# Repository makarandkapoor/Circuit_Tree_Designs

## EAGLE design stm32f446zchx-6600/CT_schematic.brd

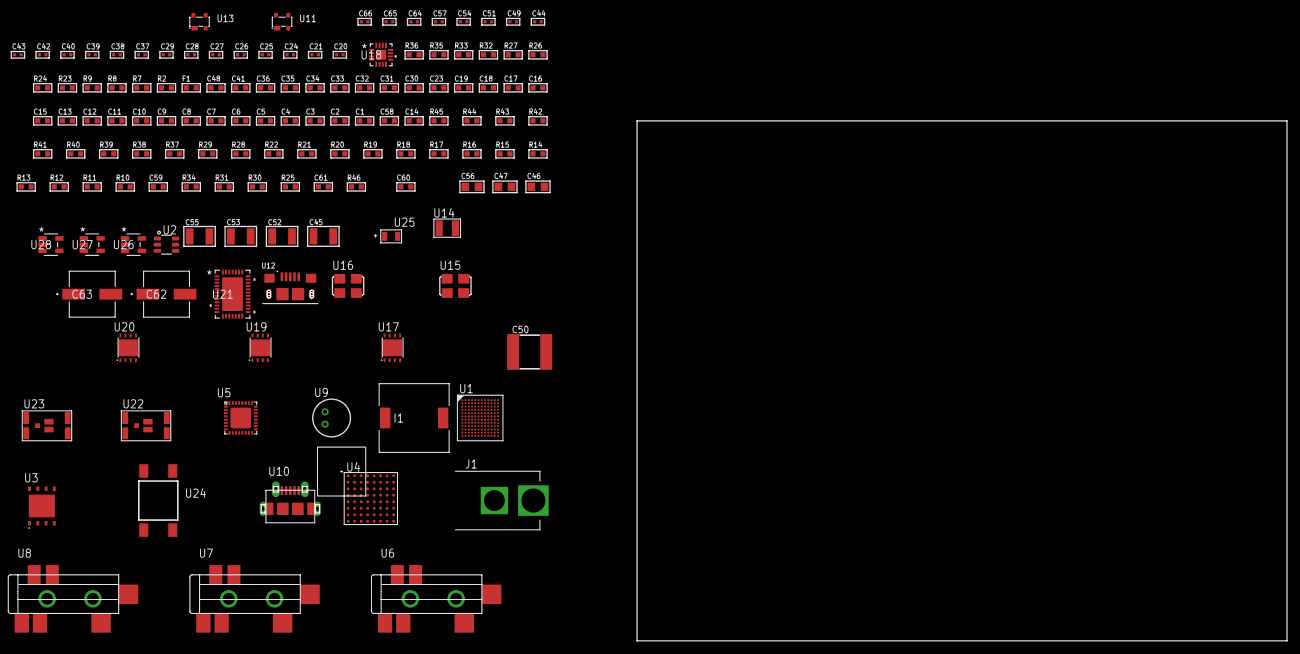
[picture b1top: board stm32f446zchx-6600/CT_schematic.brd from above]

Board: 2 copper layers, 137 parts (0 on the bottom side), 131 nets, no tracks yet.

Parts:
C1, C16, C23, C30, C31, C32, C33, C34, C35, C36, C41, C48: 1e-06; C0603
C2, C3, C4, C5, C6, C7, C8, C9, C10, C11, C12, C13, C17, C18, C19: 1e-07; C0603
C14: 4.7e-06; C0603
C15: 1e-08; C0603
C20, C21: 1e-11; C0402
C24, C26, C28, C37, C38, C39, C40, C49, C57: 1e-07; C0402
C25, C27, C29, C42, C43, C44, C51, C54, C64, C65, C66: 1e-08; C0402
C45, C52, C53, C55: 1e-05; C1210
C46, C47, C56: 1e-05; C0805
C50: 6.8e-05; 2220
C58: 2.2e-06; C0603
C59: 2.45e-08; R0603
C60: 2.8258362168397e-09; R0603
C61: 7.105e-09; R0603
C62, C63: 0.0001; EXV-9H
F1: 240.0; L0603
I1: 5.2e-06; DR1040
J1: PJ-037B; PJ-037B_PACKAGE
R2, R27, R33, R36: 1000.0; R0603
R7, R8, R9: 4700.0; R0603
R10: 47000.0; R0603
R11, R12, R13, R14, R15, R16, R17, R18, R19, R20, R21, R22, R37, R39, R40, R43, R44, R45: 10000.0; R0603
R23, R24: 1270.0; R0603
R25, R31, R34: 100000.0; R0603
R26, R35: 200.0; R0603
R28: 20000.0; R0603
R29: 91000.0; R0603
R30: 300000.0; R0603
R32: 3900.0; R0603
R38: 75000.0; R0603
R41, R42: 95300.0; R0603
R46: 120272.72727273; R0603
U1: STM32F446ZCH6; UFBGA144
U2: MAX4995AAUT+T; SOT-23-6
U3: MX25R6435FZAIH0; WSON-8-PAD
U4: PC28F512P33BFD
U5: SGTL5000XNAA3; QFN-32
U6, U7, U8: SJ-43515TS-SMT-TR
U9: WM-64PCT; WM-64PC
U10: 47590-0001; MICRO_USB_AB
U11, U13: prtr5v0u2ax; SOT143B
U12: 10118193-0001LF; FCI_10118193-0001LF
U14: ABS07-32.768KHZ-7-T
U15: ASFL-24.57MHZ-NCS; ASFL1
U16: ASFL1-25MHZ-NCS; ASFL1
U17, U19, U20: LP3878SDX-ADJ/NOPB; WSON-8
U18: LTC3601EUD#PBF; QFN-16_EP
U21: LTC2928CUHF#PBF; QFN-38_UHF
U22, U23: IRF8306MTRPbF; IRF8306MTRPBF
U24: 4-1437565-2; SW_4-1437565-2
U25: Q65110A2395; LGM67K-G1J2-24-Z
U26, U27, U28: nc7sz125m5x; NC7SZ125M5X

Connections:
CLK_CRYSTAL_U1_B1: C20.1, U1.B1, U14.1
CLK_CRYSTAL_U1_C1: C21.1, U1.C1, U14.2
CLK_U1_D1: U1.D1, U16.3
CLK_U5_21: U5.21, U15.3
GND: C1.2, C2.2, C3.2, C4.2, C5.2, C6.2, C7.2, C8.2, C9.2, C10.2, C11.2, C12.2, C13.2, C14.2, C15.2, C16.2, C17.2, C18.2, C19.2, C20.2, C21.2, C23.2, C24.2, C25.2, C26.2, C27.2, C28.2, C29.2, C37.2, C38.2, C39.2, C40.2, C41.2, C42.2, C43.2, C44.2, C45.2, C46.2, C47.2, C48.2, C50.1, C50.2, C51.2, C52.2, C53.2, C54.2, C55.2, C56.2, C57.2, C58.2, C59.2, C60.2, C61.2, C62.2, C63.2, C64.2, C65.2, C66.2, J1.2, R2.2, R10.2, R11.2, R15.2, R24.2, R27.2, R28.2, R30.2, R33.2, R36.2, R38.2, R41.2, R42.2, R43.2, R44.2, R45.2, U1.D2, U1.E6, U1.E7, U1.G4, U1.G8, U1.G10, U1.H6, U1.J1, U1.K1, U2.2, U3.4, U3.PAD, U4.B2, U4.H2, U4.H4, U4.H6, U5.1, U5.3, U5.7, U5.EXP, U7.1, U8.1, U9.2, U10.5, U10.6, U10.7, U10.8, U10.9, U11.1, U12.5, U12.6, U12.7, U12.8, U12.9, U13.1, U15.2, U16.2, U17.3, U17.PAD, U18.1, U18.9, U18.17, U19.3, U19.PAD, U20.3, U20.PAD, U21.8, U21.9, U21.10, U21.12, U21.13, U21.24, U21.25, U21.30, U21.32, U21.39, U25.C, U26.1, U26.3, U27.1, U27.3, U28.1, U28.3
NET_U1_D5: R11.1, U1.D5
NET_U1_E5: R12.1, U1.E5
NET_U1_F1: R9.1, U1.F1, U28.4
NET_U1_G9: C19.1, U1.G9
NET_U1_H5: R13.1, U1.H5
NET_U1_M1: C15.1, C16.1, F1.1, U1.L1, U1.M1
NET_U1_M11: U24.3, U24.4
NET_U2_3: R10.1, U2.3
NET_U3_7: R7.1, U1.F3, U3.7, U26.4
NET_U4_A4: C28.1, C29.1, U4.A4
NET_U4_C6: R21.1, U4.C6
NET_U4_D4: R8.1, U4.D4, U27.4
NET_U5_10: C40.1, U5.10
NET_U5_29: R23.1, U5.29
NET_U5_31: R24.1, U5.31
NET_U6_1: U5.4, U6.1
NET_U6_2: U5.2, U6.2
NET_U6_5: U5.6, U6.5
NET_U7_2: C31.1, U7.2
NET_U7_5: C30.1, U7.5
NET_U8_2: C33.1, C34.1, U8.2
NET_U8_5: C32.1, U8.5
NET_U8_13: C33.2, C34.2
NET_U9_1: C35.1, C36.1, C41.1, U5.16, U9.1
NET_U9_15: C35.2, C36.2
NET_U17_1: C44.1, U17.1
NET_U17_6: R26.2, R27.1, U17.6
NET_U17_8: R25.1, U17.8
NET_U18_3: C49.2, I1.1, U18.3, U18.4
NET_U18_6: C49.1, U18.6
NET_U18_7: C48.1, U18.7, U18.12
NET_U18_10: R30.1, U18.10
NET_U18_11: R28.1, R29.1, U18.11
NET_U18_ATNET_3: I1.2, R29.2
NET_U19_1: C51.1, U19.1
NET_U19_6: R32.2, R33.1, U19.6
NET_U19_8: R31.1, U19.8
NET_U20_1: C54.1, U20.1
NET_U20_6: R35.2, R36.1, U20.6
NET_U20_8: R34.1, U20.8
NET_U21_3: R44.1, U21.3
NET_U21_6: R41.1, U21.6
NET_U21_7: R42.1, U21.7
NET_U21_16: R43.1, R46.1, U21.16
NET_U21_18: R40.1, U21.18
NET_U21_19: R39.1, U21.19, U21.20
NET_U21_21: R37.1, R38.1, U21.21, U26.2, U27.2, U28.2
NET_U21_22: C57.1, R37.2, R39.2, R40.2, U21.11, U21.22
NET_U21_26: C60.1, U21.26
NET_U21_27: C59.1, U21.27
NET_U21_28: C61.1, U21.28
NET_U21_38: R45.1, U21.38
NET_U22_3: U21.2, U22.3
NET_U23_3: U21.37, U23.3
NET_U24_1: R2.1, U24.1, U24.2
PROC_FMC_A0: U1.C3, U4.A1
PROC_FMC_A1: U1.C4, U4.B1
PROC_FMC_A2: U1.D4, U4.C1
PROC_FMC_A3: U1.E2, U4.D1
PROC_FMC_A4: U1.E3, U4.D2
PROC_FMC_A5: U1.E4, U4.A2
PROC_FMC_A6: U1.L5, U4.C2
PROC_FMC_A7: U1.K5, U4.A3
PROC_FMC_A8: U1.M6, U4.B3
PROC_FMC_A9: U1.L6, U4.C3
PROC_FMC_A10: U1.K6, U4.D3
PROC_FMC_A11: U1.J6, U4.C4
PROC_FMC_A12: U1.J12, U4.A5
PROC_FMC_A13: U1.J11, U4.B5
PROC_FMC_A14: U1.J10, U4.C5
PROC_FMC_A15: U1.H12, U4.D7
PROC_FMC_A16: U1.H9, U4.D8
PROC_FMC_A17: U1.L10, U4.A7
PROC_FMC_A18: U1.K10, U4.B7
PROC_FMC_A19: U1.A2, U4.C7
PROC_FMC_A20: U1.B2, U4.C8
PROC_FMC_A21: U1.B3, U4.A8
PROC_FMC_A22: U1.B4, U4.G1
PROC_FMC_A23: U1.A3, U4.H8
PROC_FMC_A24: U1.D7, U4.B6
PROC_FMC_CLK: U1.D9, U4.E6
PROC_FMC_D0: U1.K11, U4.F2
PROC_FMC_D1: U1.K12, U4.E2
PROC_FMC_D2: U1.E10, U4.G3
PROC_FMC_D3: U1.D10, U4.E4
PROC_FMC_D4: U1.M7, U4.E5
PROC_FMC_D5: U1.L7, U4.G5
PROC_FMC_D6: U1.K7, U4.G6
PROC_FMC_D7: U1.J7, U4.H7
PROC_FMC_D8: U1.H8, U4.E1
PROC_FMC_D9: U1.J8, U4.E3
PROC_FMC_D10: U1.K8, U4.F3
PROC_FMC_D11: U1.L8, U4.F4
PROC_FMC_D12: U1.M8, U4.F5
PROC_FMC_D13: U1.L9, U4.H5
PROC_FMC_D14: U1.K9, U4.G7
PROC_FMC_D15: U1.J9, U4.E7
PROC_FMC_NE2: R19.1, U1.E8, U4.B4
PROC_FMC_NL: R18.1, U1.D6, U4.F6
PROC_FMC_NOE: R20.1, U1.C9, U4.F8
PROC_FMC_NWAIT: U1.A8, U4.F7
PROC_FMC_NWE: R22.1, U1.B9, U4.G8
PROC_GPIO_TO_U1_USB_FAULT: R14.1, U1.A4, U2.6
PROC_GPIO_TO_U1_VBUS_EN: R15.1, U1.A1, U2.4
PROC_I2S1_CK: U1.A7, U5.24
PROC_I2S1_SD: U1.B6, U5.26
PROC_I2S1_WS: U1.A10, U5.23
PROC_QUADSPI_BK1_IO0: U1.E11, U3.5
PROC_QUADSPI_BK1_IO1: U1.B11, U3.2
PROC_QUADSPI_BK1_IO2: R17.1, U1.F2, U3.3
PROC_QUADSPI_BK1_NCS: R16.1, U1.C6, U3.1
PROC_QUADSPI_CLK: U1.J5, U3.6
PROC_USB_OTG_FS_DM: U1.C12, U10.2, U11.3
PROC_USB_OTG_FS_DP: U1.B12, U10.3, U11.2
PROC_USB_OTG_FS_ID: U1.D11, U10.4
PROC_USB_OTG_FS_VBUS: U1.D12, U2.1, U10.1, U11.4
PROC_USB_OTG_HS_DM: U12.2, U13.3
PROC_USB_OTG_HS_DP: U12.3, U13.2
PROC_USB_OTG_HS_VBUS: U12.1, U13.4
VCC_14V6: C58.1, C62.1, C63.1, J1.1, R46.2, U21.23, U22.1, U22.2, U22.6, U22.7, U23.1, U23.2, U23.6, U23.7
VCC_S1_14V6: C45.1, C47.1, C52.1, R25.2, R31.2, U17.4, U18.15, U18.16, U19.4, U22.4, U22.5
VCC_S2_14V6: C55.1, R34.2, U20.4, U23.4, U23.5
VCC_TIER1_1V2: C18.1, C37.1, C46.1, R26.1, U1.H7, U5.30, U17.5
VCC_TIER1_3V3: C1.1, C2.1, C3.1, C4.1, C5.1, C6.1, C7.1, C8.1, C9.1, C10.1, C11.1, C12.1, C13.1, C14.1, C17.1, C23.1, C24.1, C25.1, C26.1, C27.1, C38.1, C39.1, C42.1, C43.1, C50.2, C64.1, C65.1, C66.1, F1.2, I1.2, R7.2, R8.2, R9.2, R12.2, R13.2, R14.2, R16.2, R17.2, R18.2, R19.2, R20.2, R21.2, R22.2, R23.2, R29.2, U1.C2, U1.C11, U1.D3, U1.F4, U1.F5, U1.F6, U1.F7, U1.F8, U1.F9, U1.F10, U1.G5, U1.G6, U1.G7, U3.8, U4.A6, U4.D5, U4.D6, U4.G4, U4.H3, U5.5, U5.20, U15.4, U16.4, U18.8, U26.5, U27.5, U28.5
VCC_TIER1_5V0: C53.1, R32.1, U2.5, U19.5
VCC_TIER2_1V2: C56.1, R35.1, U20.5

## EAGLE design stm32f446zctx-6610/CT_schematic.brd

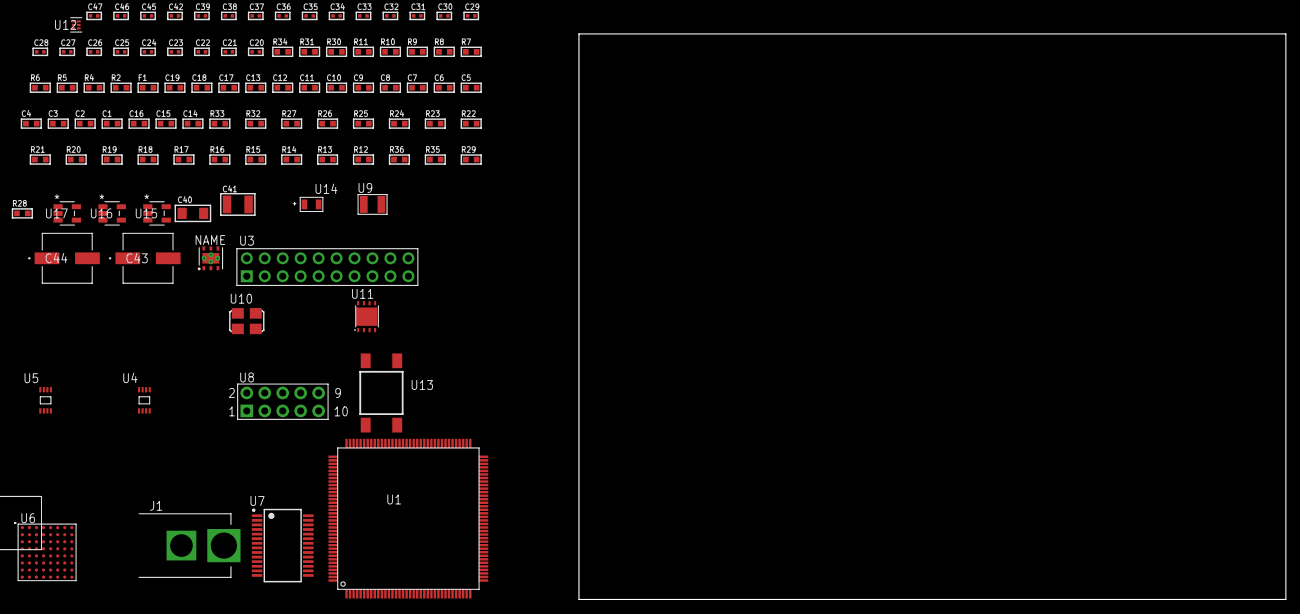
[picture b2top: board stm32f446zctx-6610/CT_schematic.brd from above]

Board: 2 copper layers, 100.0 x 80.0 mm, 100 parts (0 on the bottom side), 97 nets, no tracks yet.

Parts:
C1, C18: 1e-06; C0603
C2, C3, C4, C5, C6, C7, C8, C9, C10, C11, C12, C13, C19: 1e-07; C0603
C14: 4.7e-06; C0603
C15, C16: 2.2e-06; C0603
C17: 1e-08; C0603
C20, C21: 1e-11; C0402
C22, C25, C26, C28, C30, C32, C38, C39, C45, C46, C47: 1e-08; C0402
C23, C24, C27, C29, C31, C33, C34, C35, C36, C37, C42: 1e-07; C0402
C40: 1e-05; C1206
C41: 1e-05; C1210
C43, C44: 0.0001; EXV-9H
F1: 240.0; L0603
J1: PJ-037B; PJ-037B_PACKAGE
R2, R31: 1000.0; R0603
R4, R5: 4700.0; R0603
R6, R7, R8, R9, R10, R11: 2200.0; R0603
R12, R13, R14, R15, R16, R17, R18, R19, R20, R21, R22, R23, R24, R25, R26, R27, R32, R33: 10000.0; R0603
R28, R29: 100000.0; R0603
R30: 2231.0; R0603
R34: 9100.0; R0603
R35: 680000.0; R0603
R36: 120000.0; R0603
U1: STM32F446ZCT6; LQFP144
U2: HDC1080DMBR; WSON-6
U3: TST-110-05-T-D-RA
U4: 24AA01T-I/MNY; TDFN-8/6MM
U5: 24AA64T-I/MNY; TDFN-8/6MM
U6: PC28F512P33BFD
U7: ST3241EBPR; SSOP-28
U8: HTSS-105-01-G-D
U9: ABS07-32.768KHZ-7-T
U10: ASFL1-25MHZ-NCS; ASFL1
U11: LP3878SDX-ADJ/NOPB; WSON-8
U12: TPS3895ADRYR; SON-6
U13: 4-1437565-2; SW_4-1437565-2
U14: Q65110A2395; LGM67K-G1J2-24-Z
U15, U16, U17: nc7sz125m5x; NC7SZ125M5X

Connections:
CLK_CRYSTAL_U1_8: C20.1, U1.8, U9.1
CLK_CRYSTAL_U1_9: C21.1, U1.9, U9.2
CLK_U1_23: U1.23, U10.3
GND: C1.2, C2.2, C3.2, C4.2, C5.2, C6.2, C7.2, C8.2, C9.2, C10.2, C11.2, C12.2, C13.2, C14.2, C15.2, C16.2, C17.2, C18.2, C19.2, C20.2, C21.2, C22.2, C23.2, C24.2, C25.2, C26.2, C27.2, C28.2, C29.2, C30.2, C31.2, C32.2, C33.2, C36.2, C37.2, C38.2, C39.2, C40.2, C41.2, C42.2, C43.2, C44.2, C45.2, C46.2, C47.2, J1.2, R2.2, R12.2, R19.2, R20.2, R21.2, R31.2, R34.2, R36.2, U1.16, U1.31, U1.38, U1.51, U1.61, U1.83, U1.94, U1.107, U1.120, U1.130, U2.2, U2.PAD, U3.4, U3.6, U3.8, U3.10, U3.12, U3.14, U3.16, U3.18, U3.20, U4.4, U5.4, U5.7, U6.B2, U6.H2, U6.H4, U6.H6, U7.23, U7.25, U8.9, U10.2, U11.3, U11.PAD, U12.2, U14.C, U15.2, U15.3, U16.1, U16.3, U17.1, U17.3
NET_U1_25: R5.1, U1.25, U17.4
NET_U1_33: C17.1, C18.1, F1.1, U1.32, U1.33
NET_U1_69: R8.1, U1.69, U5.6
NET_U1_70: R9.1, U1.70, U5.5
NET_U1_71: C15.1, U1.71
NET_U1_99: R11.1, U1.99, U4.5
NET_U1_100: R10.1, U1.100, U4.6
NET_U1_106: C16.1, U1.106
NET_U1_136: R6.1, U1.136, U2.6
NET_U1_138: R12.1, U1.138
NET_U1_140: R7.1, U1.140, U2.1
NET_U1_142: U13.3, U13.4
NET_U1_143: R13.1, U1.143
NET_U3_19: R19.1, U3.19
NET_U5_1: R20.1, U5.1
NET_U5_2: R21.1, U5.2
NET_U5_3: R22.1, U5.3
NET_U6_A4: C31.1, C32.1, U6.A4
NET_U6_C6: R26.1, U6.C6
NET_U6_D4: R4.1, U6.D4, U16.4
NET_U7_1: C35.1, U7.1
NET_U7_2: C35.2, U7.2
NET_U7_3: C37.1, U7.3
NET_U7_22: R28.1, U7.22
NET_U7_24: C34.2, U7.24
NET_U7_27: C36.1, U7.27
NET_U7_28: C34.1, U7.28
NET_U8_3: U7.4, U8.3
NET_U8_4: U7.5, U8.4
NET_U8_5: U7.9, U8.5
NET_U8_6: U7.10, U8.6
NET_U11_1: C39.1, U11.1
NET_U11_6: R30.2, R31.1, U11.6
NET_U11_8: R29.1, U11.8
NET_U12_1: R33.1, R34.1, U12.1
NET_U12_3: R35.2, R36.1, U12.3
NET_U12_4: R32.1, U12.4, U15.4, U16.2, U17.2
NET_U13_1: R2.1, U13.1, U13.2
PROC_FMC_A0: U1.10, U6.A1
PROC_FMC_A1: U1.11, U6.B1
PROC_FMC_A2: U1.12, U6.C1
PROC_FMC_A3: U1.13, U6.D1
PROC_FMC_A4: U1.14, U6.D2
PROC_FMC_A5: U1.15, U6.A2
PROC_FMC_A6: U1.50, U6.C2
PROC_FMC_A7: U1.53, U6.A3
PROC_FMC_A8: U1.54, U6.B3
PROC_FMC_A9: U1.55, U6.C3
PROC_FMC_A10: U1.56, U6.D3
PROC_FMC_A11: U1.57, U6.C4
PROC_FMC_A12: U1.87, U6.A5
PROC_FMC_A13: U1.88, U6.B5
PROC_FMC_A14: U1.89, U6.C5
PROC_FMC_A15: U1.90, U6.D7
PROC_FMC_A16: U1.80, U6.D8
PROC_FMC_A17: U1.81, U6.A7
PROC_FMC_A18: U1.82, U6.B7
PROC_FMC_A19: U1.2, U6.C7
PROC_FMC_A20: U1.3, U6.C8
PROC_FMC_A21: U1.4, U6.A8
PROC_FMC_A22: U1.5, U6.G1
PROC_FMC_A23: U1.1, U6.H8
PROC_FMC_A24: U1.128, U6.B6
PROC_FMC_CLK: U1.117, U6.E6
PROC_FMC_D0: U1.85, U6.F2
PROC_FMC_D1: U1.86, U6.E2
PROC_FMC_D2: U1.114, U6.G3
PROC_FMC_D3: U1.115, U6.E4
PROC_FMC_D4: U1.58, U6.E5
PROC_FMC_D5: U1.59, U6.G5
PROC_FMC_D6: U1.60, U6.G6
PROC_FMC_D7: U1.63, U6.H7
PROC_FMC_D8: U1.64, U6.E1
PROC_FMC_D9: U1.65, U6.E3
PROC_FMC_D10: U1.66, U6.F3
PROC_FMC_D11: U1.67, U6.F4
PROC_FMC_D12: U1.68, U6.F5
PROC_FMC_D13: U1.77, U6.H5
PROC_FMC_D14: U1.78, U6.G7
PROC_FMC_D15: U1.79, U6.E7
PROC_FMC_NE2: R24.1, U1.124, U6.B4
PROC_FMC_NL: R23.1, U1.137, U6.F6
PROC_FMC_NOE: R25.1, U1.118, U6.F8
PROC_FMC_NWAIT: U1.122, U6.F7
PROC_FMC_NWE: R27.1, U1.119, U6.G8
PROC_SYS_JTCK_SWCLK: R17.1, U1.109, U3.9
PROC_SYS_JTDI: R15.1, U1.110, U3.5
PROC_SYS_JTDO_SWO: U1.133, U3.13
PROC_SYS_JTMS_SWDIO: R16.1, U1.105, U3.7
PROC_SYS_JTRST: R14.1, U1.134, U3.3
RST_OUT_U3_SRESET_B: R18.1, U3.15, U15.1
VCC_S1_7V8: C40.1, C43.1, C44.1, J1.1, R29.2, U11.4
VCC_TIER1_3V3: C1.1, C2.1, C3.1, C4.1, C5.1, C6.1, C7.1, C8.1, C9.1, C10.1, C11.1, C12.1, C13.1, C14.1, C19.1, C22.1, C23.1, C24.1, C25.1, C26.1, C27.1, C28.1, C29.1, C30.1, C33.1, C38.1, C41.1, C42.1, C45.1, C46.1, C47.1, F1.2, R4.2, R5.2, R6.2, R7.2, R8.2, R9.2, R10.2, R11.2, R13.2, R14.2, R15.2, R16.2, R17.2, R18.2, R22.2, R23.2, R24.2, R25.2, R26.2, R27.2, R28.2, R30.1, R32.2, R33.2, R35.1, U1.6, U1.17, U1.30, U1.39, U1.52, U1.62, U1.72, U1.84, U1.95, U1.108, U1.121, U1.131, U1.144, U2.5, U3.1, U3.2, U4.7, U4.8, U5.8, U6.A6, U6.D5, U6.D6, U6.G4, U6.H3, U7.26, U10.4, U11.5, U12.6, U15.5, U16.5, U17.5

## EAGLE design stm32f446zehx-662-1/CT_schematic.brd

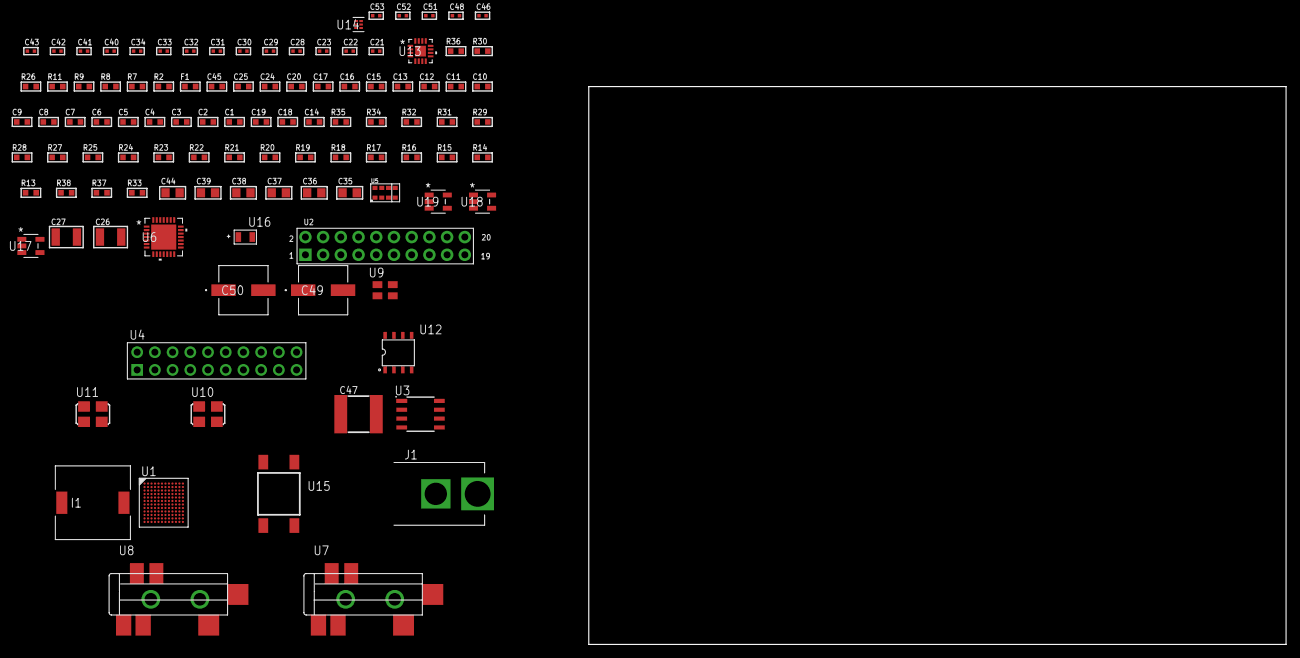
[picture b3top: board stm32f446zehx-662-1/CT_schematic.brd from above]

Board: 2 copper layers, 100.0 x 80.0 mm, 106 parts (0 on the bottom side), 60 nets, no tracks yet.

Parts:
C1, C16, C20, C24, C25, C45: 1e-06; C0603
C2, C3, C4, C5, C6, C7, C8, C9, C10, C11, C12, C13, C17: 1e-07; C0603
C14: 4.7e-06; C0603
C15: 1e-08; C0603
C18, C19: 2.2e-06; C0603
C21, C40, C41, C42, C43, C51, C52, C53: 1e-08; C0402
C22, C23, C30, C31, C32, C33, C34, C46, C48: 1e-07; C0402
C26, C27: 2.2e-05; C1210
C28, C29: 1e-09; C0402
C35, C36, C37, C38, C39, C44: 1e-05; C0805
C47: 6.8e-05; 2220
C49, C50: 0.0001; EXV-9H
F1: 240.0; L0603
I1: 3.8e-06; DR1040
J1: PJ-037B; PJ-037B_PACKAGE
R2: 1000.0; R0603
R7, R8: 4700.0; R0603
R9, R11: 2200.0; R0603
R13, R14, R15, R16, R17, R18, R19, R20, R21, R22, R23, R24, R25, R34, R35: 10000.0; R0603
R26: 22.0; R0603
R27, R28, R29: 47000.0; R0603
R30: 680.0; R0603
R31: 20000.0; R0603
R32: 91000.0; R0603
R33: 300000.0; R0603
R36: 9100.0; R0603
R37: 680000.0; R0603
R38: 120000.0; R0603
U1: STM32F446ZEH6; UFBGA144
U2: arducam_ov2640; ARDUCAM
U3: AT25M01-SSHM-T; SOIC-8
U4: TST-110-05-T-D-RA
U5: TMD27711; SMD-8
U6: WM8731CLSEFL; QFN-28
U7, U8: SJ-43515TS-SMT-TR
U9: ASEK-32.768KHz-ECST; ASEK
U10: ASFL1-12.288MHZ-EC-T; ASFL1
U11: ASFL1-25MHZ-NCS; ASFL1
U12: idt74fct38072; IDT74FCT38072
U13: LTC3601EUD#PBF; QFN-16_EP
U14: TPS3895ADRYR; SON-6
U15: 4-1437565-2; SW_4-1437565-2
U16: Q65110A2395; LGM67K-G1J2-24-Z
U17, U18, U19: nc7sz125m5x; NC7SZ125M5X

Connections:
CLK_U1_B1: U1.B1, U9.3
CLK_U1_D1: U1.D1, U12.6
CLK_U2_8: U2.8, U12.7
CLK_U6_1: U6.1, U10.3
CLK_U12_3: U11.3, U12.3
GND: C1.2, C2.2, C3.2, C4.2, C5.2, C6.2, C7.2, C8.2, C9.2, C10.2, C11.2, C12.2, C13.2, C14.2, C15.2, C16.2, C17.2, C18.2, C19.2, C20.2, C21.2, C22.2, C23.2, C24.2, C25.2, C29.2, C30.2, C31.2, C32.2, C33.2, C34.2, C35.2, C36.2, C37.2, C38.2, C39.2, C40.2, C41.2, C42.2, C43.2, C44.2, C45.2, C47.1, C47.2, C48.2, C49.2, C50.2, C51.2, C52.2, C53.2, J1.2, R2.2, R13.2, R15.2, R24.2, R27.2, R28.2, R29.2, R31.2, R33.2, R36.2, R38.2, U1.D2, U1.E6, U1.E7, U1.G4, U1.G8, U1.G10, U1.H6, U1.J1, U1.K1, U2.2, U2.20, U3.4, U4.4, U4.6, U4.8, U4.10, U4.12, U4.14, U4.16, U4.18, U4.20, U5.3, U6.4, U6.15, U6.19, U6.25, U6.26, U6.29, U7.1, U8.1, U9.2, U10.2, U11.2, U12.4, U12.5, U12.8, U13.1, U13.9, U13.17, U14.2, U16.C, U17.2, U17.3, U18.1, U18.3, U19.1, U19.3
NET_U1_B5: R11.1, U1.B5, U5.8
NET_U1_C5: R9.1, U1.C5, U5.2
NET_U1_D5: R13.1, U1.D5
NET_U1_E5: R14.1, U1.E5
NET_U1_F1: R7.1, U1.F1, U18.4
NET_U1_G9: C19.1, U1.G9
NET_U1_H5: R15.1, U1.H5
NET_U1_H7: C18.1, U1.H7
NET_U1_M1: C15.1, C16.1, F1.1, U1.L1, U1.M1
NET_U1_M12: U15.3, U15.4
NET_U2_19: R8.1, U2.19, U19.4
NET_U3_3: R16.1, U3.3
NET_U3_7: R18.1, U3.7
NET_U4_19: R24.1, U4.19
NET_U5_4: C25.1, R26.1, U5.4
NET_U5_7: R25.1, U5.7
NET_U6_20: C34.1, C39.1, U6.20
NET_U7_2: C27.1, R28.1, U7.2
NET_U7_5: C26.1, R27.1, U7.5
NET_U8_5: C28.1, C29.1, R29.1, R30.1, U8.5
NET_U13_3: C46.2, I1.1, U13.3, U13.4
NET_U13_6: C46.1, U13.6
NET_U13_7: C45.1, U13.7, U13.12
NET_U13_10: R33.1, U13.10
NET_U13_11: R31.1, R32.1, U13.11
NET_U13_ATNET_3: I1.2, R32.2
NET_U14_1: R35.1, R36.1, U14.1
NET_U14_3: R37.2, R38.1, U14.3
NET_U14_4: R34.1, U14.4, U17.4, U18.2, U19.2
NET_U15_1: R2.1, U15.1, U15.2
PROC_DCMI_D0: U1.D12, U2.18
PROC_DCMI_D1: U1.D11, U2.17
PROC_DCMI_D2: U1.A5, U2.16
PROC_DCMI_D3: U1.A4, U2.15
PROC_DCMI_D4: U1.B2, U2.14
PROC_DCMI_D5: U1.C6, U2.13
PROC_DCMI_D6: U1.B3, U2.12
PROC_DCMI_D7: U1.B4, U2.11
PROC_DCMI_D8: U1.B11, U2.10
PROC_DCMI_D9: U1.C10, U2.9
PROC_DCMI_HSYNC: U1.J3, U2.6
PROC_DCMI_PIXCLK: U1.L3, U2.7
PROC_DCMI_VSYNC: U1.D6, U2.5
PROC_I2S2_CK: U1.F12, U6.7
PROC_I2S2_SD: U1.H4, U6.8
PROC_I2S2_WS: U1.M11, U6.9, U6.11
PROC_SPI2_NSS: R17.1, U3.1
PROC_SYS_JTCK_SWCLK: R22.1, U4.9
PROC_SYS_JTDI: R20.1, U4.5
PROC_SYS_JTMS_SWDIO: R21.1, U4.7
PROC_SYS_JTRST: R19.1, U4.3
RST_OUT_U4_SRESET_B: R23.1, U4.15, U17.1
VCC_S1_11V2: C44.1, C49.1, C50.1, J1.1, U13.15, U13.16
VCC_TIER1_3V3: C1.1, C2.1, C3.1, C4.1, C5.1, C6.1, C7.1, C8.1, C9.1, C10.1, C11.1, C12.1, C13.1, C14.1, C17.1, C20.1, C21.1, C22.1, C23.1, C24.1, C30.1, C31.1, C32.1, C33.1, C35.1, C36.1, C37.1, C38.1, C40.1, C41.1, C42.1, C43.1, C47.2, C48.1, C51.1, C52.1, C53.1, F1.2, I1.2, R7.2, R8.2, R9.2, R11.2, R14.2, R16.2, R17.2, R18.2, R19.2, R20.2, R21.2, R22.2, R23.2, R25.2, R26.2, R32.2, R34.2, R35.2, R37.1, U1.C2, U1.C11, U1.D3, U1.F4, U1.F5, U1.F6, U1.F7, U1.F8, U1.F9, U1.F10, U1.G5, U1.G6, U1.G7, U2.1, U3.8, U4.1, U4.2, U5.1, U6.3, U6.5, U6.12, U6.18, U9.4, U10.4, U11.4, U12.1, U12.2, U13.8, U14.6, U17.5, U18.5, U19.5

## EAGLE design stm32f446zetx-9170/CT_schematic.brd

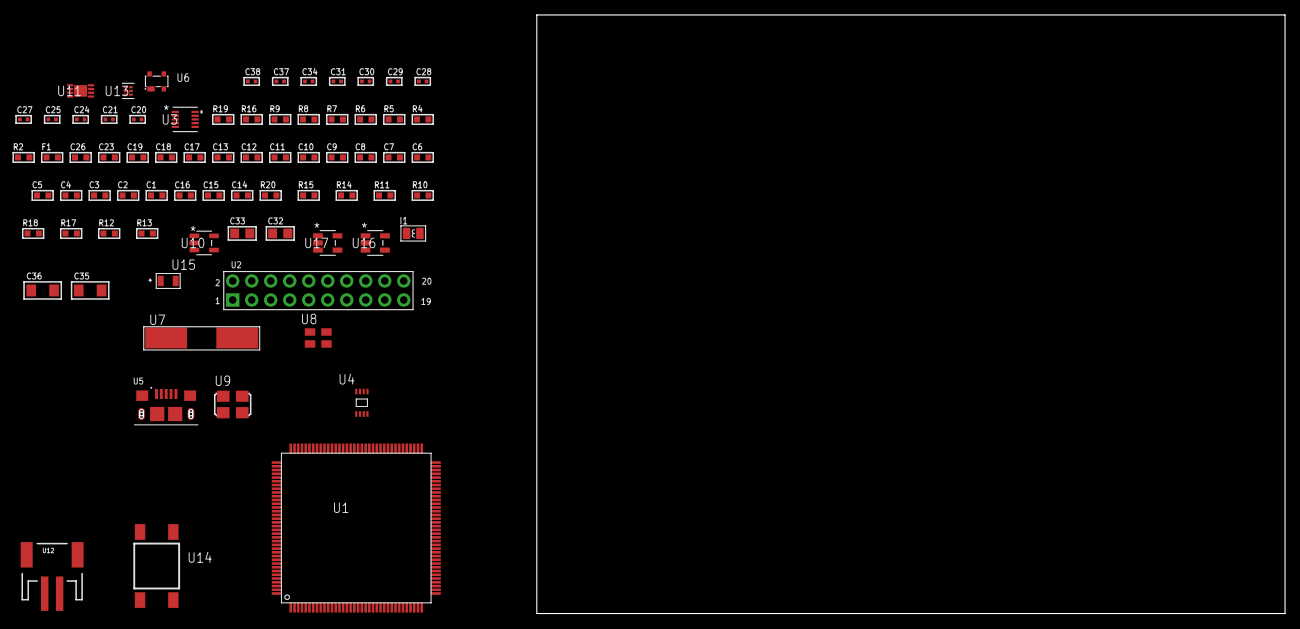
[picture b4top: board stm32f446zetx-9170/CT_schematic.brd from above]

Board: 2 copper layers, 74 parts (0 on the bottom side), 46 nets, no tracks yet.

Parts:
C1, C18, C23, C26: 1e-06; C0603
C2, C3, C4, C5, C6, C7, C8, C9, C10, C11, C12, C13, C19: 1e-07; C0603
C14: 4.7e-06; C0603
C15, C16: 2.2e-06; C0603
C17: 1e-08; C0603
C20, C21: 1e-11; C0402
C24, C25, C27, C28, C34: 1e-07; C0402
C29, C30, C31, C37, C38: 1e-08; C0402
C32, C33: 1e-05; C0805
C35, C36: 1e-05; C1206
F1: 240.0; L0603
I1: 1.5e-06; L0806
R2: 1000.0; R0603
R4, R5: 4700.0; R0603
R6, R7, R8, R9: 2200.0; R0603
R10, R11, R14, R15, R20: 10000.0; R0603
R12: 220000.0; R0603
R13: 1000000.0; R0603
R16: 9100.0; R0603
R17: 680000.0; R0603
R18: 120000.0; R0603
R19: 2000.0; R0603
U1: STM32F446ZET6; LQFP144
U2: arducam_ov2640; ARDUCAM
U3: MAG3110FCR1; DFN-10
U4: 24AA01T-I/MNY; TDFN-8/6MM
U5: 10118193-0001LF; FCI_10118193-0001LF
U6: prtr5v0u2ax; SOT143B
U7: ABLS-25.000MHZ-B2F-T
U8: ASEK-32.768KHz-ECST; ASEK
U9: ASFL1-25MHZ-NCS; ASFL1
U10: ltc3406es5; TSOT-23-5
U11: MCP73831T-2ACI/MC; DFN8_2X3MC
U12: S2B-PH-SM4-TB(LF)(SN); JST-2-SMD
U13: TPS3895ADRYR; SON-6
U14: 4-1437565-2; SW_4-1437565-2
U15: Q65110A2395; LGM67K-G1J2-24-Z
U16, U17: nc7sz125m5x; NC7SZ125M5X

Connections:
CLK_CRYSTAL_U1_23: C20.1, U1.23, U7.1
CLK_CRYSTAL_U1_24: C21.1, U1.24, U7.2
CLK_U1_8: U1.8, U8.3
CLK_U2_8: U2.8, U9.3
GND: C1.2, C2.2, C3.2, C4.2, C5.2, C6.2, C7.2, C8.2, C9.2, C10.2, C11.2, C12.2, C13.2, C14.2, C15.2, C16.2, C17.2, C18.2, C19.2, C20.2, C21.2, C23.2, C24.2, C25.2, C26.2, C27.2, C28.2, C29.2, C30.2, C31.2, C32.2, C33.1, C33.2, C34.2, C35.2, C36.2, C37.2, C38.2, R2.2, R10.2, R12.2, R16.2, R18.2, R19.2, U1.16, U1.31, U1.38, U1.51, U1.61, U1.83, U1.94, U1.107, U1.120, U1.130, U2.2, U2.20, U3.5, U3.10, U4.4, U4.7, U5.5, U5.6, U5.7, U5.8, U5.9, U6.1, U8.2, U9.2, U10.2, U11.6, U11.9, U12.2, U13.2, U15.C, U16.1, U16.3, U17.1, U17.3
INPUT_USBPOWER_5V: C35.1, R20.2, U5.1, U6.4, U11.1, U11.2
NET_U1_10: R9.1, U1.10, U4.5
NET_U1_11: R8.1, U1.11, U4.6
NET_U1_25: R4.1, U1.25, U16.4
NET_U1_33: C17.1, C18.1, F1.1, U1.32, U1.33
NET_U1_71: C15.1, U1.71
NET_U1_106: C16.1, U1.106
NET_U1_136: R6.1, U1.136, U3.7
NET_U1_137: R7.1, U1.137, U3.6
NET_U1_138: R10.1, U1.138
NET_U1_142: U14.3, U14.4
NET_U1_143: R11.1, U1.143
NET_U2_19: R5.1, U2.19, U17.4
NET_U3_1: C24.1, U3.1
NET_U3_4: C27.1, U3.4
NET_U10_3: I1.1, U10.3
NET_U10_5: R12.1, R13.1, U10.5
NET_U10_ATNET_3: I1.2, R13.2
NET_U11_5: R20.1, U11.5
NET_U11_8: R19.1, U11.8
NET_U13_1: R15.1, R16.1, U13.1
NET_U13_3: R17.2, R18.1, U13.3
NET_U13_4: R14.1, U13.4, U16.2, U17.2
NET_U14_1: R2.1, U14.1, U14.2
PROC_DCMI_D0: U1.96, U2.18
PROC_DCMI_D1: U1.97, U2.17
PROC_DCMI_D2: U1.98, U2.16
PROC_DCMI_D3: U1.99, U2.15
PROC_DCMI_D4: U1.3, U2.14
PROC_DCMI_D5: U1.117, U2.13
PROC_DCMI_D6: U1.4, U2.12
PROC_DCMI_D7: U1.5, U2.11
PROC_DCMI_D8: U1.111, U2.10
PROC_DCMI_D9: U1.113, U2.9
PROC_DCMI_HSYNC: U1.40, U2.6
PROC_DCMI_PIXCLK: U1.42, U2.7
PROC_DCMI_VSYNC: U1.124, U2.5
PROC_USB_OTG_FS_DM: U5.2, U6.3
PROC_USB_OTG_FS_DP: U5.3, U6.2
VCC_S1_3V7: C32.1, C36.1, U10.4, U11.3, U11.4, U12.1
VCC_TIER1_3V3: C1.1, C2.1, C3.1, C4.1, C5.1, C6.1, C7.1, C8.1, C9.1, C10.1, C11.1, C12.1, C13.1, C14.1, C19.1, C23.1, C25.1, C26.1, C28.1, C29.1, C30.1, C31.1, C33.2, C34.1, C37.1, C38.1, F1.2, I1.2, R4.2, R5.2, R6.2, R7.2, R8.2, R9.2, R11.2, R13.2, R14.2, R15.2, R17.1, U1.6, U1.17, U1.30, U1.39, U1.52, U1.62, U1.72, U1.84, U1.95, U1.108, U1.121, U1.131, U1.144, U2.1, U3.2, U3.8, U4.8, U8.4, U9.4, U13.6, U16.5, U17.5

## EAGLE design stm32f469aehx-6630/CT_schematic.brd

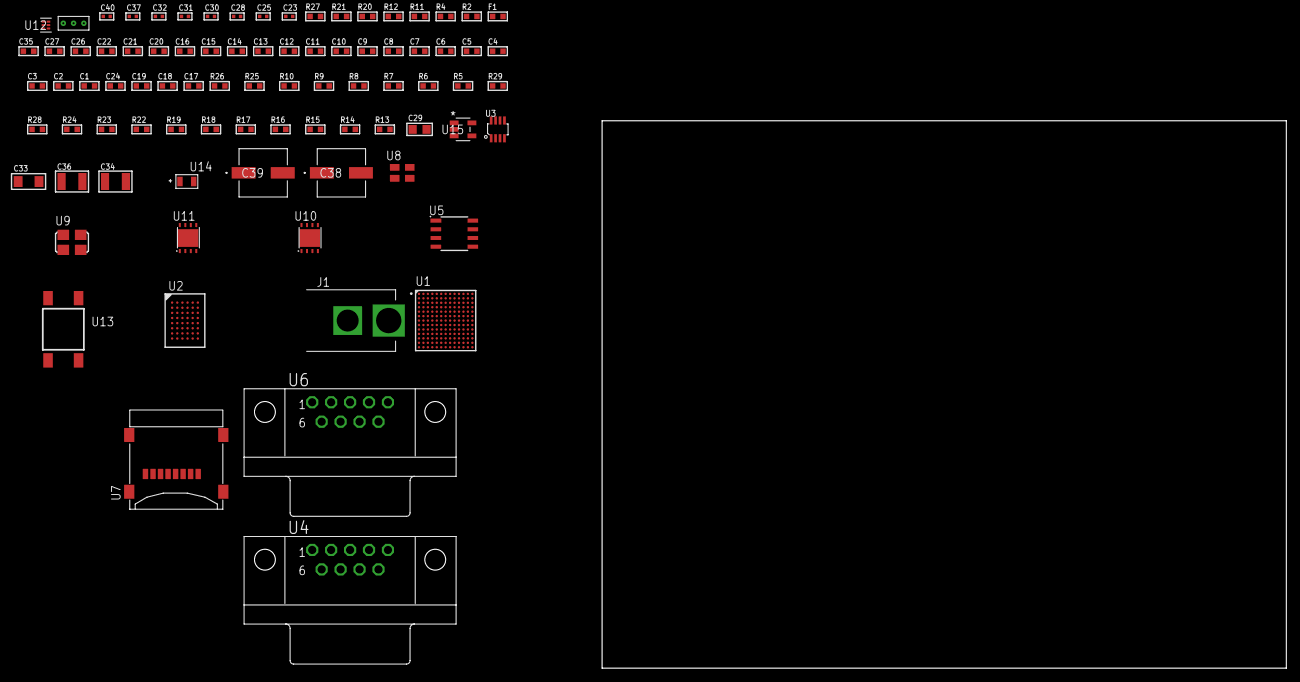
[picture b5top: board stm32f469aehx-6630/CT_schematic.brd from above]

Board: 2 copper layers, 100.0 x 80.0 mm, 85 parts (0 on the bottom side), 79 nets, no tracks yet.

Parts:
C1, C21, C26, C27, C35: 1e-06; C0603
C2, C3, C4, C5, C6, C7, C8, C9, C10, C11, C12, C13, C14, C15, C16, C22: 1e-07; C0603
C17: 4.7e-06; C0603
C18, C19, C24: 2.2e-06; C0603
C20: 1e-08; C0603
C23, C25, C28, C37: 1e-07; C0402
C29: 1e-05; C0805
C30, C31, C32, C40: 1e-08; C0402
C33: 1e-05; C1206
C34, C36: 1e-05; C1210
C38, C39: 0.0001; EXV-9H
F1: 240.0; L0603
J1: PJ-037B; PJ-037B_PACKAGE
R2, R21: 1000.0; R0603
R4: 4700.0; R0603
R5, R6, R7, R8, R9, R10, R25, R26: 10000.0; R0603
R11, R12: 120.0; R0603
R13, R14, R15, R16, R17, R18, R19, R22, R24: 100000.0; R0603
R20: 2231.0; R0603
R23: 300000.0; R0603
R27: 9100.0; R0603
R28: 680000.0; R0603
R29: 120000.0; R0603
U1: STM32F469AEH6; UFBGA169
U2: CY62147GE30-45BVXI; VFBGA48
U3: MAX3051EKA+T; SOT-23-8
U4, U6: 182-009-113R531; 182-009-MALE
U5: MCP2562-E/SN; SOIC-8
U7: 0472192001; MOLEX_47219-2001
U8: ASEK-32.768KHz-ECST; ASEK
U9: ASFL1-25MHZ-NCS; ASFL1
U10: LP3878SDX-ADJ/NOPB; WSON-8
U11: LP2951ACSDX/NOPB; WSON-8
U12: TPS3895ADRYR; SON-6
U13: 4-1437565-2; SW_4-1437565-2
U14: Q65110A2395; LGM67K-G1J2-24-Z
U15: nc7sz125m5x; NC7SZ125M5X
U16: Dummy; DUMMY_PACKAGE_186

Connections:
CLK_U1_E1: U1.E1, U8.3
CLK_U1_G2: U1.G2, U9.3
GND: C1.2, C2.2, C3.2, C4.2, C5.2, C6.2, C7.2, C8.2, C9.2, C10.2, C11.2, C12.2, C13.2, C14.2, C15.2, C16.2, C17.2, C18.2, C19.2, C20.2, C21.2, C22.2, C23.2, C24.2, C25.2, C26.2, C27.2, C28.2, C29.2, C30.2, C31.2, C32.2, C33.2, C34.2, C35.2, C36.2, C37.2, C38.2, C39.2, C40.2, J1.2, R2.2, R21.2, R24.2, R27.2, R29.2, U1.D11, U1.E3, U1.F5, U1.F8, U1.G7, U1.G9, U1.H11, U1.J1, U1.J2, U1.J6, U1.J7, U1.J10, U1.K11, U1.M9, U2.D1, U2.E6, U3.2, U3.8, U4.5, U5.2, U5.8, U6.5, U7.6, U7.G1, U7.G2, U7.G3, U7.G4, U8.2, U9.2, U10.3, U10.PAD, U11.3, U11.4, U11.PAD, U12.2, U14.C, U15.1, U15.3, U16.1
NET_U1_A5: R6.1, U1.A5
NET_U1_C3: R5.1, U1.C3
NET_U1_D12: C19.1, U1.D12
NET_U1_H2: R4.1, U1.H2, U15.4
NET_U1_J3: C20.1, C21.1, F1.1, U1.J3
NET_U1_L5: R7.1, U1.L5
NET_U1_N9: C18.1, U1.N9
NET_U1_N13: U13.3, U13.4
NET_U3_6: R11.2, U3.6
NET_U4_2: R11.2, U3.6, U4.2
NET_U4_3: R11.1, U3.7, U4.3
NET_U5_6: R12.2, U5.6
NET_U6_2: R12.2, U5.6, U6.2
NET_U6_3: R12.1, U5.7, U6.3
NET_U10_1: C32.1, U10.1
NET_U10_6: R20.2, R21.1, U10.6
NET_U10_8: R19.1, U10.8
NET_U11_5: R22.1, U11.5
NET_U11_7: R23.2, R24.1, U11.7
NET_U12_1: R26.1, R27.1, U12.1
NET_U12_3: R28.2, R29.1, U12.3
NET_U12_4: R25.1, U12.4, U15.2
NET_U13_1: R2.1, U13.1, U13.2
PROC_CAN1_RX: U1.A13, U5.4
PROC_CAN1_TX: U1.A12, U5.1
PROC_CAN2_RX: U1.D5, U3.4
PROC_CAN2_TX: U1.C5, U3.1
PROC_FMC_A0: U1.F3, U2.A3
PROC_FMC_A1: U1.G3, U2.A4
PROC_FMC_A2: U1.G5, U2.A5
PROC_FMC_A3: U1.H4, U2.B3
PROC_FMC_A4: U1.L4, U2.B4
PROC_FMC_A5: U1.H3, U2.C3
PROC_FMC_A6: U1.N5, U2.C4
PROC_FMC_A7: U1.M4, U2.D4
PROC_FMC_A8: U1.H5, U2.H2
PROC_FMC_A9: U1.M6, U2.H3
PROC_FMC_A10: U1.N6, U2.H4
PROC_FMC_A11: U1.M7, U2.H5
PROC_FMC_A12: U1.F13, U2.G3
PROC_FMC_A13: U1.F12, U2.G4
PROC_FMC_A14: U1.E13, U2.F3
PROC_FMC_A15: U1.E12, U2.F4
PROC_FMC_A16: U1.M11, U2.E4
PROC_FMC_A17: U1.M13, U2.D3
PROC_FMC_D0: U1.L12, U2.B6
PROC_FMC_D1: U1.L13, U2.C5
PROC_FMC_D2: U1.C9, U2.C6
PROC_FMC_D3: U1.C7, U2.D5
PROC_FMC_D4: U1.N7, U2.E5
PROC_FMC_D5: U1.G6, U2.F5
PROC_FMC_D6: U1.H6, U2.F6
PROC_FMC_D7: U1.H7, U2.G6
PROC_FMC_D8: U1.K7, U2.B1
PROC_FMC_D9: U1.L7, U2.C1
PROC_FMC_D10: U1.J8, U2.C2
PROC_FMC_D11: U1.K8, U2.D2
PROC_FMC_D12: U1.L8, U2.E2
PROC_FMC_D13: U1.L10, U2.F2
PROC_FMC_D14: U1.M10, U2.F1
PROC_FMC_D15: U1.L11, U2.G1
PROC_FMC_NBL0: U1.A4, U2.A1
PROC_FMC_NE2: R9.1, U1.E6, U2.B5
PROC_FMC_NOE: R8.1, U1.C6, U2.A2
PROC_FMC_NWE: R10.1, U1.B7, U2.G5
PROC_SDIO_CK: R14.1, U1.A9, U7.5
PROC_SDIO_CMD: R13.1, U1.B8, U7.3
PROC_SDIO_D0: R15.1, U1.E10, U7.7
PROC_SDIO_D1: R16.1, U1.G10, U7.8
PROC_SDIO_D2: R17.1, U1.C10, U7.1
PROC_SDIO_D3: R18.1, U1.B9, U7.2
PROC_TIM1_CH1: U1.D8, U16.3
PROC_TIM1_CH2: U1.E8, U16.2
VCC_S1_9V7: C33.1, C35.1, C38.1, C39.1, J1.1, R19.2, U10.4, U11.8
VCC_TIER1_3V3: C1.1, C2.1, C3.1, C4.1, C5.1, C6.1, C7.1, C8.1, C9.1, C10.1, C11.1, C12.1, C13.1, C14.1, C15.1, C16.1, C17.1, C22.1, C23.1, C24.1, C25.1, C27.1, C28.1, C29.1, C30.1, C31.1, C34.1, C37.1, C40.1, F1.2, R4.2, R5.2, R6.2, R7.2, R8.2, R9.2, R10.2, R13.2, R14.2, R15.2, R16.2, R17.2, R18.2, R20.1, R25.2, R26.2, R28.1, U1.D3, U1.D10, U1.E5, U1.F4, U1.F7, U1.G8, U1.G11, U1.J4, U1.K6, U1.K10, U1.K13, U1.L6, U1.L9, U2.D6, U2.E1, U3.3, U5.5, U7.4, U8.4, U9.4, U10.5, U12.6, U15.5
VCC_TIER1_5V0: C26.1, C36.1, R22.2, R23.1, U5.3, U11.1
